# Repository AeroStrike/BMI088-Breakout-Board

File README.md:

# BMI088 Breakout Board
Breakout Board for the Bosch BMI088 IMU (I2C Version)   
(Designed In Altium)  
BOM Is Included With Supplier Links  
Datasheet Is Included   
Footprints For Components Are Located Here: https://github.com/AeroStrike/Altium-In-House-Libraries   
## Sensor Information  
Sensor: BMI088 IMU (https://www.digikey.com/en/products/detail/bosch-sensortec/BMI088/8634936)  
Datasheet: https://www.bosch-sensortec.com/media/boschsensortec/downloads/datasheets/bst-bmi088-ds001.pdf  
# BMI088 Breakout I2C Version
Current Production Revision: V1.0  
Current Prototype Revision: V1.1
## V1.0 Details 
First Production Release   
### Size 
Size (PCB): 13.6mm Length x 10.8mm Width x 1.6mm Height  
Size (With Components): 13.6mm Length x 10.8mm Width x 3mm Height
### Weight 
Weight (PCB): 0.4 Grams  
Weight (With Components): 0.5 Grams 
### Features 
Contains all necessary outputs for I2C Communications  
Accessible Interrupts On Header Pins  
Header Pin Spacing Adapted For Optimal Breadboard Mounting (2.54mm Pitch, ~10.16 Pin Spacing)  
## V1.1 Details 
Thinner PCB than V1.0   
### Size 
Size (PCB): Not Obtained Yet 
Size (With Components): Not Obtained Yet   
### Weight 
Weight (PCB): Not Obtained Yet   
Weight (With Components): Not Obtained Yet   
### Features 
Same board as V1.0, but with a thinner PCB.
### IMPORTANT NOTE!!!
On the bottom side of the board you will see two separate solder jumper pins. These connect/disconnect the pull up resistors for your I2C lines. If somewhere else on your design you already have pull up resistors for your I2C lines, then you don´t need to do anything, aka leave them unsoldered. If you need to use the pull up resistors, simply just solder the two pads together. One jumper is for the SCL line, and the other is for SDA. If you would like your boards to come with presoldered jumpers, please just let me know immediately after your order at aerostrikeex@gmail.com and I will solder it for you!!
# Other Future Versions
All are available for custom order, for specificed weight and size needs. Not normally stocked, and require a bit more lead time and cost to sell. If you are also the first customer buying these specific versions, I will have to design them, so please take into account 3-4 extra days max on the lead time: 
- BMI088 SPI Breakout 
- SMD Mounted BMI088 Breakout SPI (For When Every Millimeter Matters) 
- SMD Mounted BMI088 Breakout I2C (For When Every Millimeter Matters)   

If you have custom specifications, please contact me (aerostrikeex@gmail.com) for details. The design is easily configurable, so it will not cost 100s of dollars and weeks to redesign and order your custom boards!   

# Mass/Bulk Orders
If you would like to buy bulk orders of the breakout (more than what I have listed in stock on the AeroStrike Online Store, please contact me and I will set up cheaper shipping and costs for you, and see if I can find the supply of sensors available (The BMI088 is out of stock almost everywhere as of September 2021). 
# BMI088 Library
Library for BMI088 IMU:
https://github.com/bolderflight/bmi088-arduino 
# License
This product is open sourced, and is free for use in any application, and is free to modify and change. If you have any suggestions to make to the product, email us at aerostrikeex@gmail.com, and if you use this product for a project, please email us so we can see the cool things that our products are being used for. All we ask is that you give credit where credit is due.

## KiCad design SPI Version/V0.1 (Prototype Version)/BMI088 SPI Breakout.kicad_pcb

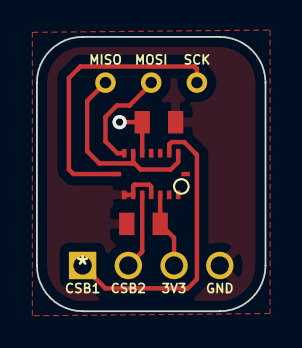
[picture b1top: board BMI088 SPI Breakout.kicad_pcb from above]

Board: 2 copper layers, 12.7 x 15.2 mm, 5 parts (0 on the bottom side), 7 nets.

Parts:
C1, C2: 0.1uF; CL21B104KBFNNNE
J1: 61300311121; 1x3_Male_Header
J2: CONN4_104346_P384XP092_TEC; 104346-2
U1: QFN_BMI085_BOS; BMI088

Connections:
+3V3: C1.1, C2.1, J2.3, U1.3, U1.11
CSB_ACCEL: J2.1, U1.14
CSB_GYRO: J2.2, U1.5
GND: C1.2, C2.2, J2.4, U1.4, U1.6, U1.7
MISO: J1.3, U1.10, U1.15
MOSI: J1.2, U1.9
SCK: J1.1, U1.8

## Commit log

2021-08-21 Create fdgfdg
2021-08-21 Create V0.1 (Prototype Version)
2021-08-21 Create Placeholder
2021-08-21 Add V0.1 KiCad Files
2021-08-21 Add V0.1 CAD Model
2021-09-07 Update README.md
    Added I2C version, special versions, and bulk order details
2021-09-07 Update README.md
    Spelling Fix
2021-09-08 Update README.md
    Add description for I2C jumpers
2021-09-11 Add files via upload
    V0.1 BOM
2021-09-11 Placeholder
2021-09-15 Update README.md
    Updated Bulk Order Details
2021-09-15 Update README.md
    Deleted Unnecessary BMI088 Library Information
2021-09-15 Update README.md
    Added Custom Order Details Note
2021-09-15 Update README.md
    Changed PCB Design Software Status
2021-09-15 Update README.md
    Fixed I2C Weight And Size Tab Formatting
2021-09-15 Update README.md
    Fixed I2C Version Number Formatting
2021-09-16 Update README.md
    Update Size And Weight
2021-09-16 Add files via upload
    Datasheet 0.5
2021-09-20 Update README.md
    Add Library Repository Link
2021-09-20 Update README.md
    Deleted SPI Information
2021-09-20 Delete BMI088 I2C Breakout V1.0 Schematic PNG.png
    Accidentally Uploaded Uncropped Version
2021-09-20 Add files via upload
    Corrected Cropped Image
2021-09-20 Delete BMI088 I2C Breakout V1.0 Schematic PNG.png
    Still Not Correct :|
2021-09-20 Update README.md
    Added V1.1 Details
2021-09-20 Update README.md
    Formatting Fix
